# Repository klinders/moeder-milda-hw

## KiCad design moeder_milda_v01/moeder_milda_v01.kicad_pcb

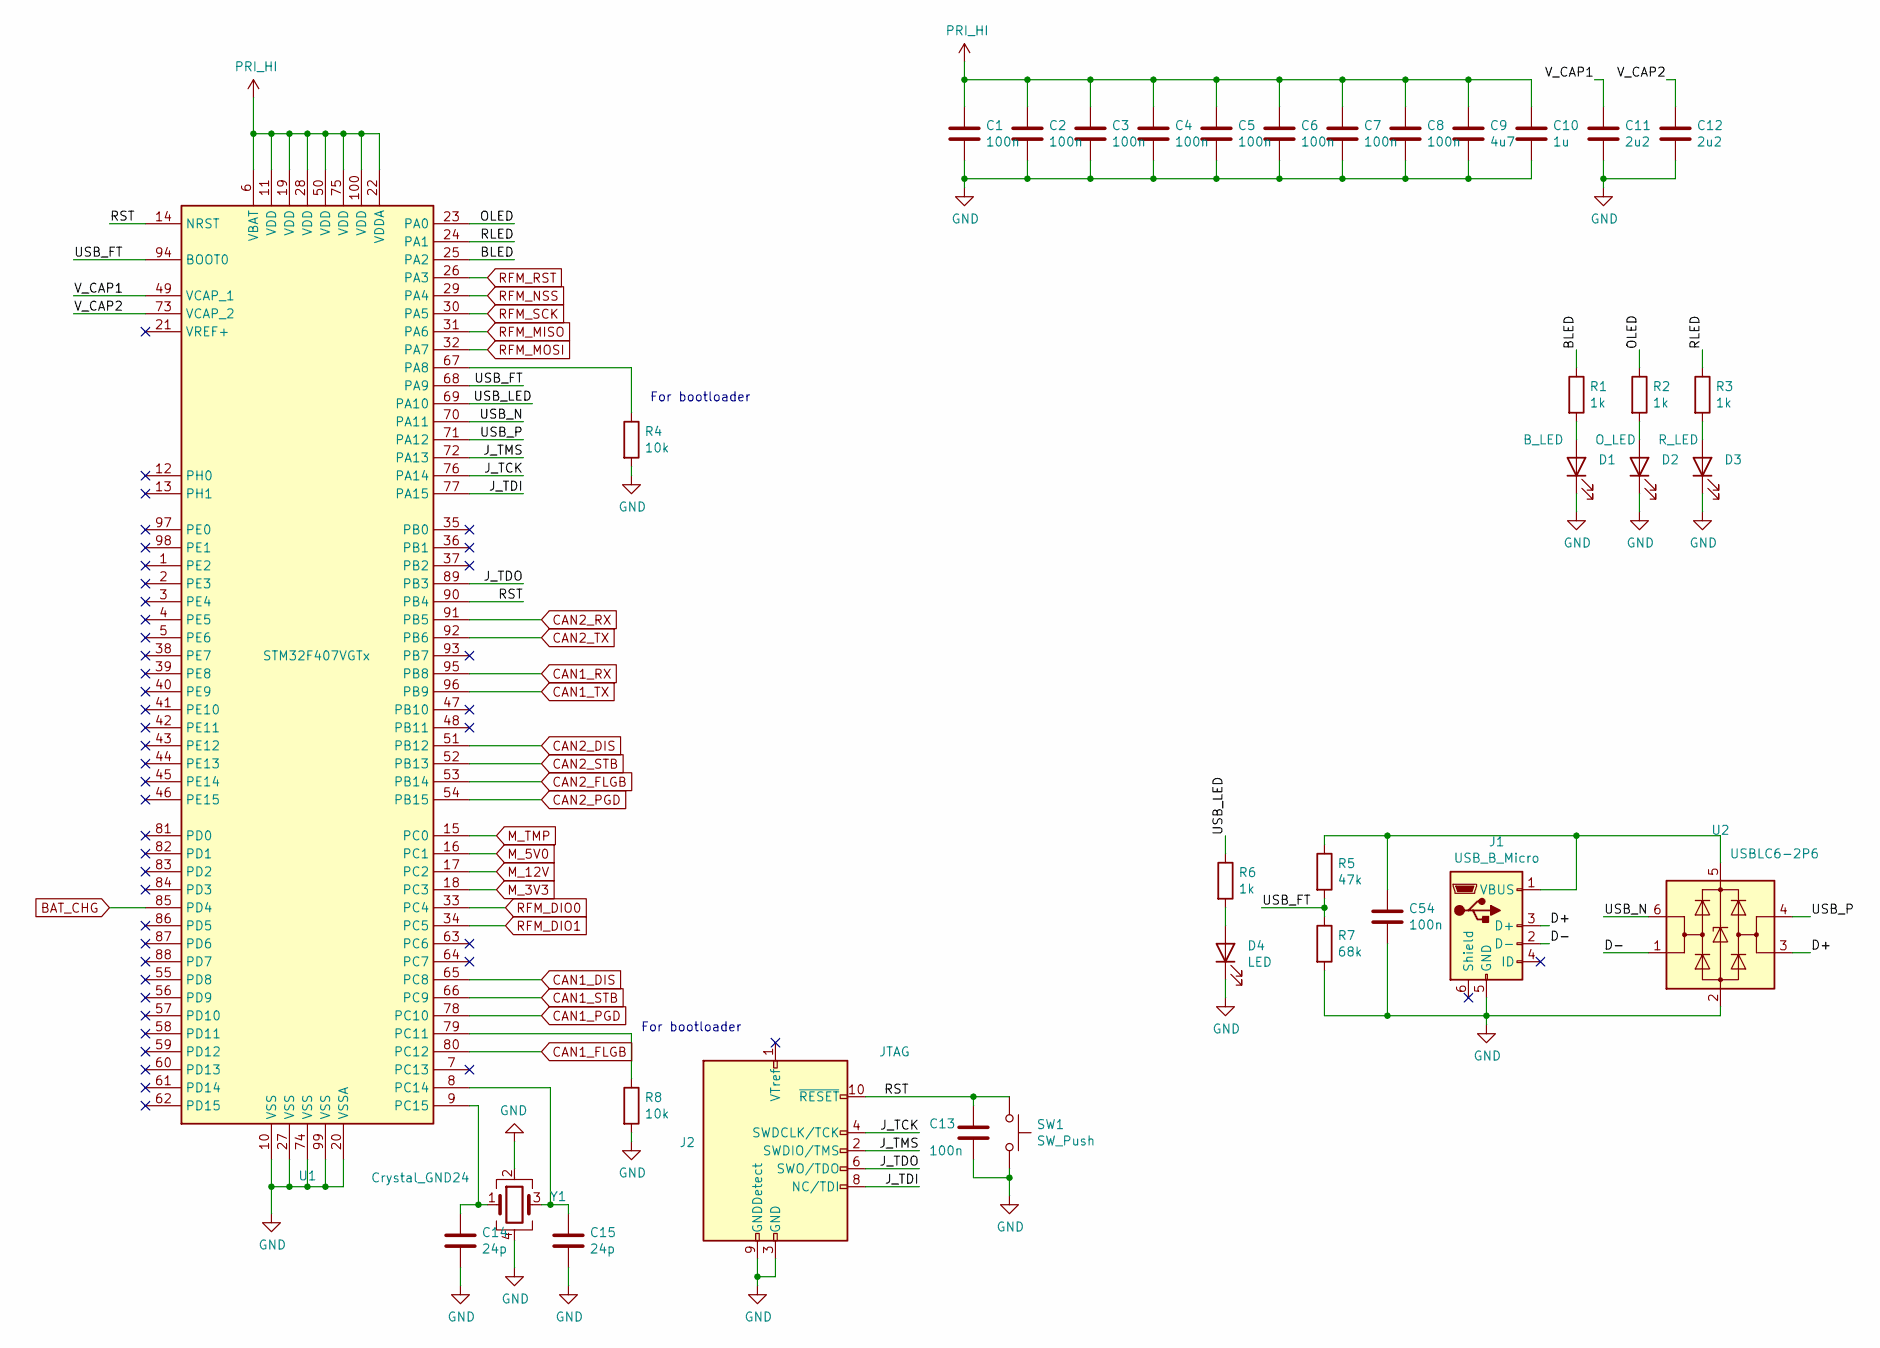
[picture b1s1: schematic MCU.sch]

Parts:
C1, C2, C3, C4, C5, C6, C7, C8, C13, C54: 100n; C_0603_1608Metric_Pad1.05x0.95mm_HandSolder; DigiKey 399-1099-1-ND
C9: 4u7; C_0805_2012Metric_Pad1.15x1.40mm_HandSolder; DigiKey 490-14466-1-ND
C10: 1u; C_0603_1608Metric_Pad1.05x0.95mm_HandSolder; DigiKey 1276-6524-1-ND
C11, C12: 2u2; C_0603_1608Metric_Pad1.05x0.95mm_HandSolder; DigiKey 587-4864-1-ND
C14, C15: 24p; C_0603_1608Metric_Pad1.05x0.95mm_HandSolder; DigiKey 490-1336-1-ND
D1: B_LED; LED_0603_1608Metric_Pad1.05x0.95mm_HandSolder; DigiKey 475-2815-1-ND
D2: O_LED; LED_0603_1608Metric_Pad1.05x0.95mm_HandSolder; DigiKey 475-2486-2-ND
D3: R_LED; LED_0603_1608Metric_Pad1.05x0.95mm_HandSolder; DigiKey 475-2512-1-ND
D4: LED; LED_0603_1608Metric_Pad1.05x0.95mm_HandSolder; DigiKey 475-2815-1-ND
J1: USB_B_Micro; USB_Micro-B_Molex_47346-0001; DigiKey WM17141CT-ND
J2: JTAG; PinHeader_2x05_P1.27mm_Vertical; DigiKey 1175-1627-ND
R1, R2, R3, R6: 1k; R_0603_1608Metric_Pad1.05x0.95mm_HandSolder
R4, R8: 10k; R_0603_1608Metric_Pad1.05x0.95mm_HandSolder
R5: 47k; R_0603_1608Metric_Pad1.05x0.95mm_HandSolder
R7: 68k; R_0603_1608Metric_Pad1.05x0.95mm_HandSolder
SW1: SW_Push; SW_SPST_B3S-1000; DigiKey SW836CT-ND
U1: STM32F407VGTx; LQFP-100_14x14mm_P0.5mm; DigiKey 497-11605-ND
U2: USBLC6-2P6; SOT-666; DigiKey 497-5026-1-ND
Y1: Crystal_GND24; Crystal_SMD_Abracon_ABM3B-4Pin_5.0x3.2mm; DigiKey 535-9720-1-ND

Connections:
/MCU/BLED: R1.1, U1.25 (PA2)
/MCU/D+: J1.3 (D+), U2.3 (I/O2)
/MCU/D-: J1.2 (D-), U2.1 (I/O1)
/MCU/J_TCK: J2.4 (SWDCLK/TCK), U1.76 (PA14)
/MCU/J_TDI: J2.8 (NC/TDI), U1.77 (PA15)
/MCU/J_TDO: J2.6 (SWO/TDO), U1.89 (PB3)
/MCU/J_TMS: J2.2 (SWDIO/TMS), U1.72 (PA13)
/MCU/OLED: R2.1, U1.23 (PA0)
/MCU/RLED: R3.1, U1.24 (PA1)
/MCU/RST: C13.1, J2.10 (~RESET~), SW1.1, U1.14 (NRST), U1.90 (PB4)
/MCU/USB_FT: R5.2, R7.1, U1.68 (PA9), U1.94 (BOOT0)
/MCU/USB_LED: R6.1, U1.69 (PA10)
/MCU/USB_N: U1.70 (PA11), U2.6 (I/O1)
/MCU/USB_P: U1.71 (PA12), U2.4 (I/O2)
/MCU/V_CAP1: C11.1, U1.49 (VCAP_1)
/MCU/V_CAP2: C12.1, U1.73 (VCAP_2)
BAT_CHG: U1.85 (PD4); also elsewhere on the board
CAN1_DIS: U1.65 (PC8); also elsewhere on the board
CAN1_FLGB: U1.80 (PC12); also elsewhere on the board
CAN1_PGD: U1.78 (PC10); also elsewhere on the board
CAN1_RX: U1.95 (PB8); also elsewhere on the board
CAN1_STB: U1.66 (PC9); also elsewhere on the board
CAN1_TX: U1.96 (PB9); also elsewhere on the board
CAN2_DIS: U1.51 (PB12); also elsewhere on the board
CAN2_FLGB: U1.53 (PB14); also elsewhere on the board
CAN2_PGD: U1.54 (PB15); also elsewhere on the board
CAN2_RX: U1.91 (PB5); also elsewhere on the board
CAN2_STB: U1.52 (PB13); also elsewhere on the board
CAN2_TX: U1.92 (PB6); also elsewhere on the board
GND: C1.2, C2.2, C3.2, C4.2, C5.2, C6.2, C7.2, C8.2, C9.2, C10.2, C11.2, C12.2, C13.2, C14.2, C15.2, C54.2, D1.1 (K), D2.1 (K), D3.1 (K), D4.1 (K), J1.5 (GND), J2.3 (GND), J2.5 (GND), J2.9 (GNDDetect), R4.2, R7.2, R8.2, SW1.2, U1.10 (VSS), U1.20 (VSSA), U1.27 (VSS), U1.74 (VSS), U1.99 (VSS), U2.2 (GND), Y1.2, Y1.4; also elsewhere on the board
M_3V3: U1.18 (PC3); also elsewhere on the board
M_5V0: U1.16 (PC1); also elsewhere on the board
M_12V: U1.17 (PC2); also elsewhere on the board
M_TMP: U1.15 (PC0); also elsewhere on the board
unnamed: C14.1, U1.9 (PC15), Y1.1
unnamed: C15.1, U1.8 (PC14), Y1.3
unnamed: C54.1, J1.1 (VBUS), R5.1, U2.5 (VBUS)
unnamed: D1.2 (A), R1.2
unnamed: D2.2 (A), R2.2
unnamed: D3.2 (A), R3.2
unnamed: D4.2 (A), R6.2
unnamed: R4.1, U1.67 (PA8)
unnamed: R8.1, U1.79 (PC11)
PRI_HI: C1.1, C2.1, C3.1, C4.1, C5.1, C6.1, C7.1, C8.1, C9.1, C10.1, U1.6 (VBAT), U1.11 (VDD), U1.19 (VDD), U1.22 (VDDA), U1.28 (VDD), U1.50 (VDD), U1.75 (VDD), U1.100 (VDD); also elsewhere on the board
RFM_DIO0: U1.33 (PC4); also elsewhere on the board
RFM_DIO1: U1.34 (PC5); also elsewhere on the board
RFM_MISO: U1.31 (PA6); also elsewhere on the board
RFM_MOSI: U1.32 (PA7); also elsewhere on the board
RFM_NSS: U1.29 (PA4); also elsewhere on the board
RFM_RST: U1.26 (PA3); also elsewhere on the board
RFM_SCK: U1.30 (PA5); also elsewhere on the board

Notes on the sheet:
For bootloader

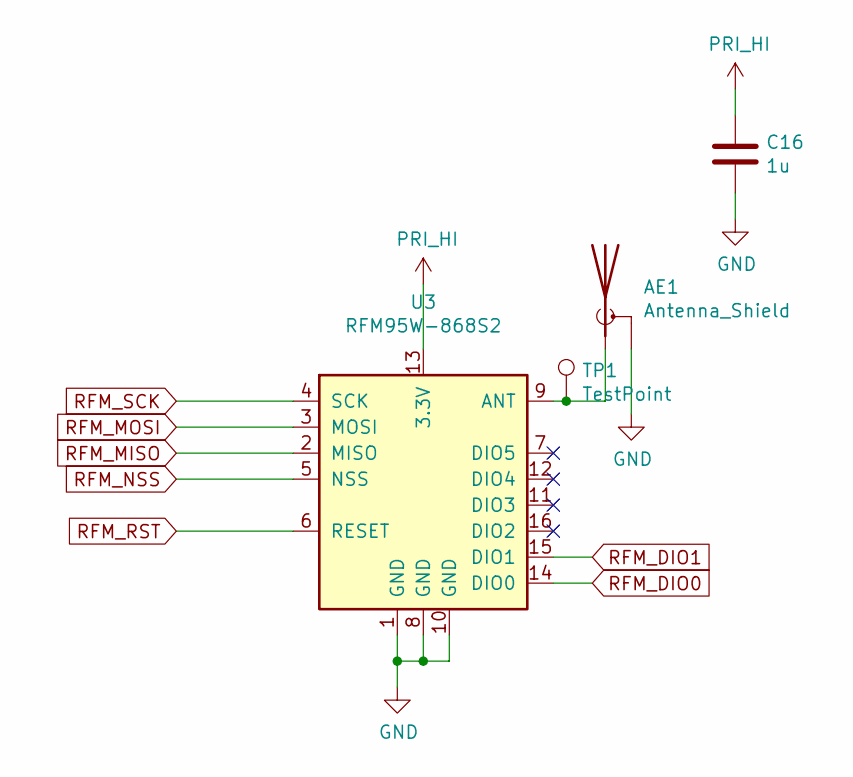
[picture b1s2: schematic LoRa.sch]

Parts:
AE1: Antenna_Shield; SMA_Molex_73251-1153_EdgeMount_Horizontal; DigiKey WM5534-ND
C16: 1u; C_0603_1608Metric_Pad1.05x0.95mm_HandSolder; DigiKey 1276-6524-1-ND
TP1: TestPoint; Curved_RF
U3: RFM95W-868S2; HOPERF_RFM9XW_SMD; DigiKey RFM95W-868S2-ND

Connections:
GND: AE1.2 (Shield), C16.2, U3.1 (GND), U3.8 (GND), U3.10 (GND); also elsewhere on the board
unnamed: AE1.1 (A), TP1.1, U3.9 (ANT)
PRI_HI: C16.1, U3.13 (3.3V); also elsewhere on the board
RFM_DIO0: U3.14 (DIO0); also elsewhere on the board
RFM_DIO1: U3.15 (DIO1); also elsewhere on the board
RFM_MISO: U3.2 (MISO); also elsewhere on the board
RFM_MOSI: U3.3 (MOSI); also elsewhere on the board
RFM_NSS: U3.5 (NSS); also elsewhere on the board
RFM_RST: U3.6 (RESET); also elsewhere on the board
RFM_SCK: U3.4 (SCK); also elsewhere on the board

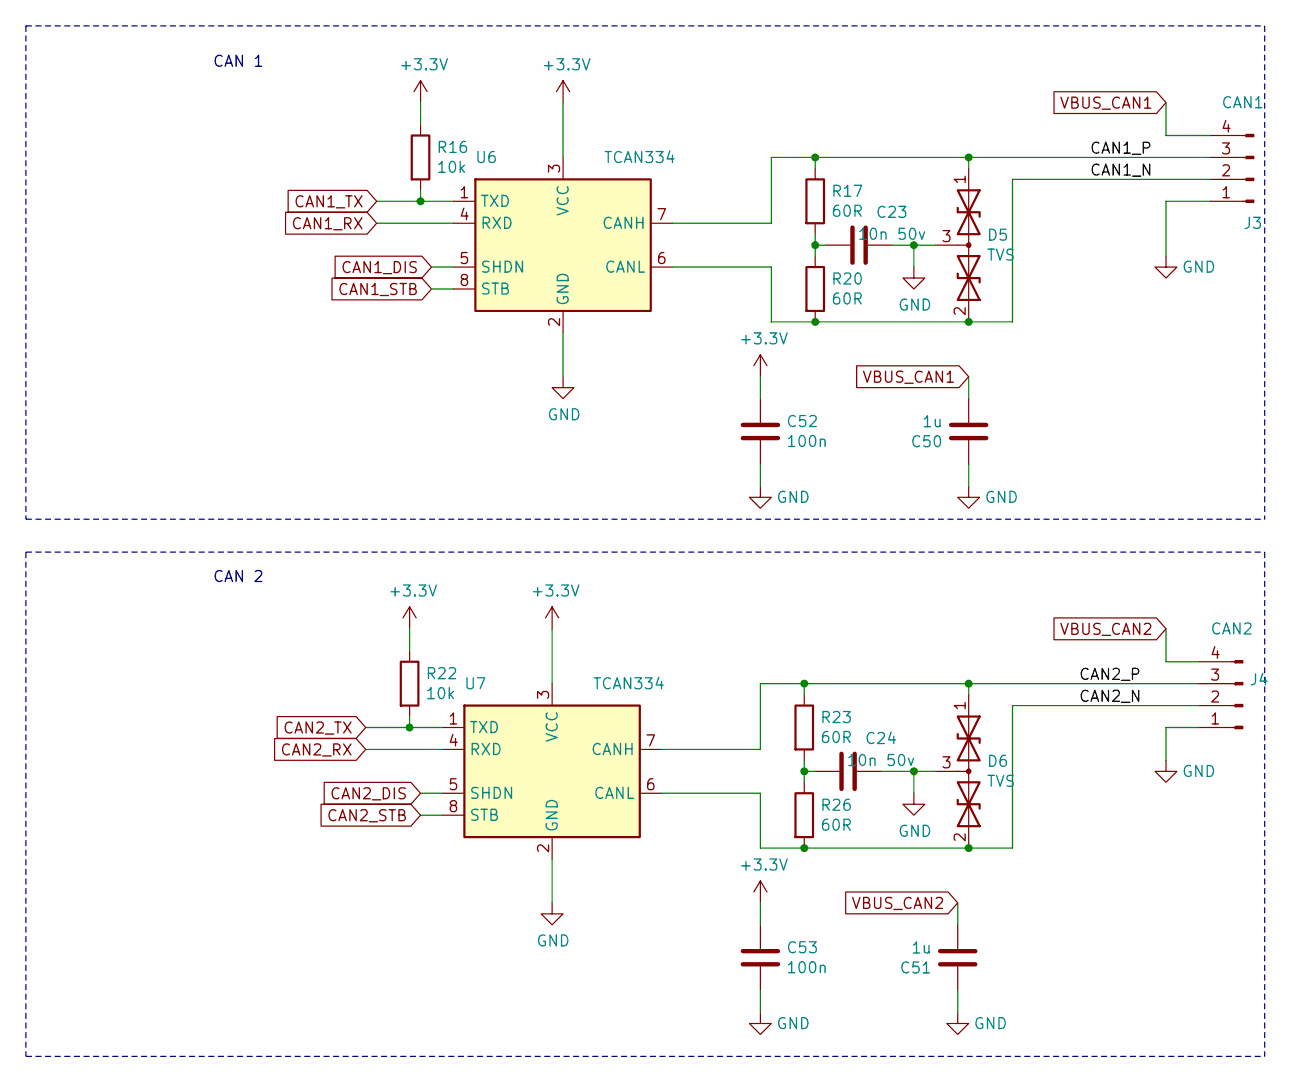
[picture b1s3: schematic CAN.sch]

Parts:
C23, C24: 10n 50v; C_0603_1608Metric_Pad1.05x0.95mm_HandSolder; DigiKey 399-17880-1-ND
C50, C51: 1u; C_0603_1608Metric_Pad1.05x0.95mm_HandSolder; DigiKey 1276-6524-1-ND
C52, C53: 100n; C_0603_1608Metric_Pad1.05x0.95mm_HandSolder; DigiKey 399-1099-1-ND
D5, D6: TVS; SOT-23_Handsoldering; DigiKey 296-24657-1-ND
J3: CAN1; PhoenixContact_MCV_1,5_4-G-5.08_1x04_P5.08mm_Vertical
J4: CAN2; PhoenixContact_MCV_1,5_4-G-5.08_1x04_P5.08mm_Vertical
R16, R22: 10k; R_0603_1608Metric_Pad1.05x0.95mm_HandSolder
R17, R20, R23, R26: 60R; R_0603_1608Metric_Pad1.05x0.95mm_HandSolder
U6, U7: TCAN334; SOIC-8_3.9x4.9mm_P1.27mm; DigiKey 296-44139-1-ND

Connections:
+3V3: C52.1, C53.1, R16.1, R22.1, U6.3 (VCC), U7.3 (VCC); also elsewhere on the board
/CAN/CAN1_N: D5.2 (A2), J3.2, R20.2, U6.6 (CANL)
/CAN/CAN1_P: D5.1 (A1), J3.3, R17.1, U6.7 (CANH)
/CAN/CAN2_N: D6.2 (A2), J4.2, R26.2, U7.6 (CANL)
/CAN/CAN2_P: D6.1 (A1), J4.3, R23.1, U7.7 (CANH)
CAN1_DIS: U6.5 (SHDN); also elsewhere on the board
CAN1_RX: U6.4 (RXD); also elsewhere on the board
CAN1_STB: U6.8 (STB); also elsewhere on the board
CAN1_TX: R16.2, U6.1 (TXD); also elsewhere on the board
CAN2_DIS: U7.5 (SHDN); also elsewhere on the board
CAN2_RX: U7.4 (RXD); also elsewhere on the board
CAN2_STB: U7.8 (STB); also elsewhere on the board
CAN2_TX: R22.2, U7.1 (TXD); also elsewhere on the board
GND: C23.2, C24.2, C50.1, C51.1, C52.2, C53.2, D5.3 (common), D6.3 (common), J3.1, J4.1, U6.2 (GND), U7.2 (GND); also elsewhere on the board
unnamed: C23.1, R17.2, R20.1
unnamed: C24.1, R23.2, R26.1
VBUS_CAN1: C50.2, J3.4; also elsewhere on the board
VBUS_CAN2: C51.2, J4.4; also elsewhere on the board

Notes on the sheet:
CAN 2
CAN 1

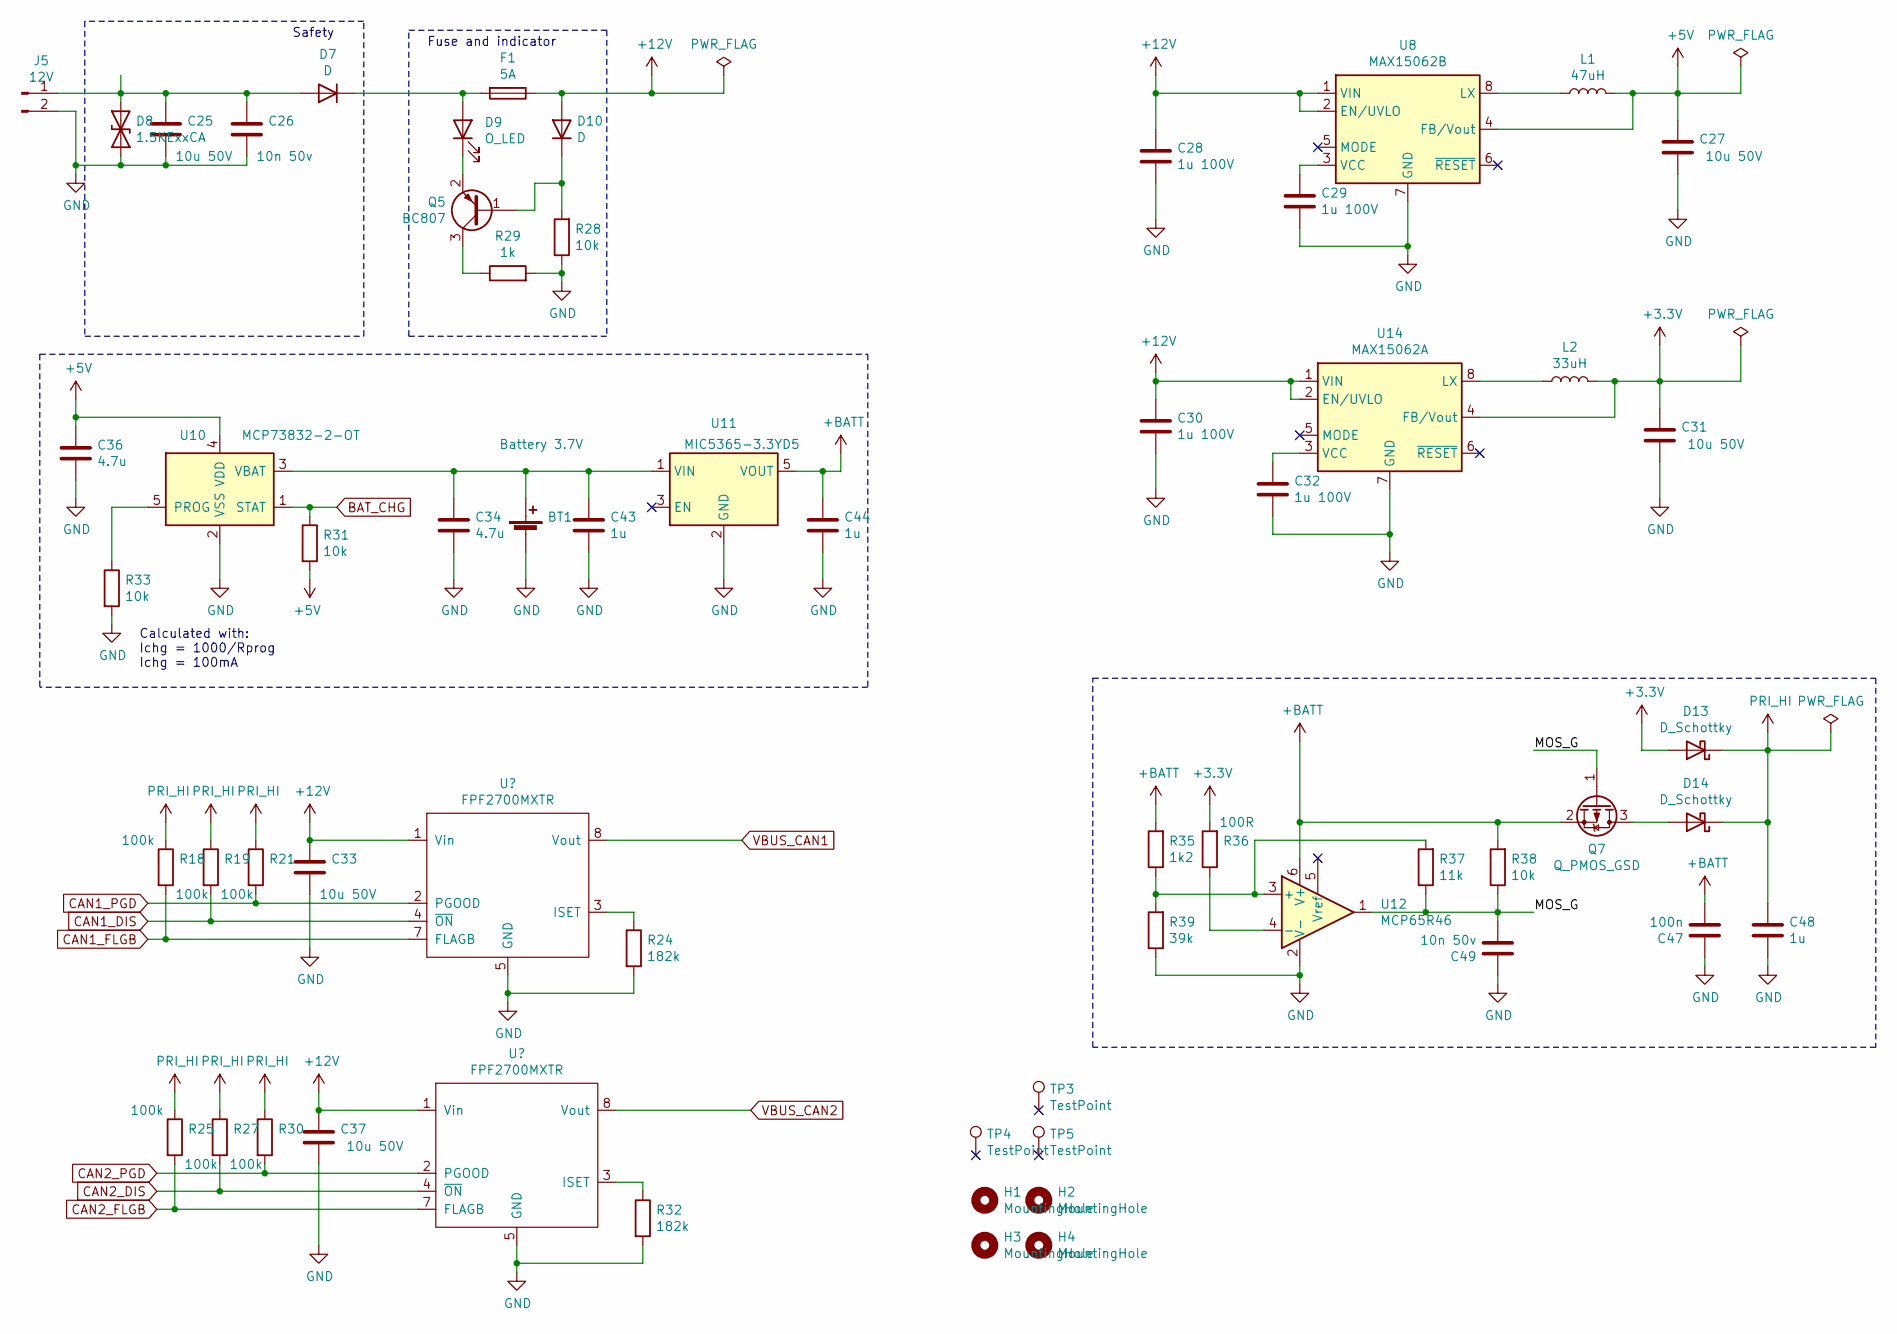
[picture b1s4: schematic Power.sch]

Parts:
BT1: Battery 3.7V; BatteryHolder_Keystone_1042_1x18650; DigiKey 36-1043-ND
C25, C27, C31, C33, C37: 10u 50V; C_1210_3225Metric_Pad1.42x2.65mm_HandSolder; DigiKey 399-11629-1-ND
C26, C49: 10n 50v; C_0603_1608Metric_Pad1.05x0.95mm_HandSolder; DigiKey 399-17880-1-ND
C28, C29, C30, C32: 1u 100V; C_1206_3216Metric_Pad1.42x1.75mm_HandSolder; DigiKey 311-1948-1-ND
C34, C36: 4.7u; C_0805_2012Metric_Pad1.15x1.40mm_HandSolder; DigiKey 490-14466-1-ND
C43, C44, C48: 1u; C_0603_1608Metric_Pad1.05x0.95mm_HandSolder; DigiKey 1276-6524-1-ND
C47: 100n; C_0603_1608Metric_Pad1.05x0.95mm_HandSolder; DigiKey 399-1099-1-ND
D7: D; D_SMC_Handsoldering; DigiKey SL54-TPMSCT-ND
D8: 1.5KExxCA; D_SMC_Handsoldering; DigiKey SMCJ17CALFCT-ND
D9: O_LED; LED_0603_1608Metric_Pad1.05x0.95mm_HandSolder; DigiKey 475-2486-2-ND
D10: D; D_SOD-323_HandSoldering; DigiKey ZHCS400CT-ND
D13, D14: D_Schottky; D_SOD-123; DigiKey 1727-3848-1-ND
F1: 5A; Fuse_1206_3216Metric_Castellated; DigiKey SF-1206F500-2CT-ND
H1, H2, H3, H4: MountingHole; MountingHole_3.2mm_M3_Pad_Via
J5: 12V; PhoenixContact_MCV_1,5_2-G-5.08_1x02_P5.08mm_Vertical
L1: 47uH; L_Bourns-SRN4018; DigiKey SRN4018TA-470MCT-ND
L2: 33uH; L_Bourns-SRN4018; DigiKey SRN4018-330MCT-ND
Q5: BC807; SOT-23_Handsoldering; DigiKey 1727-1875-1-ND
Q7: Q_PMOS_GSD; SOT-23_Handsoldering; DigiKey NTR3A30PZT1GOSCT-ND
R18, R19, R21, R25, R27, R30: 100k; R_0603_1608Metric_Pad1.05x0.95mm_HandSolder
R24, R32: 182k; R_0603_1608Metric_Pad1.05x0.95mm_HandSolder
R28, R31, R33, R38: 10k; R_0603_1608Metric_Pad1.05x0.95mm_HandSolder
R29: 1k; R_0603_1608Metric_Pad1.05x0.95mm_HandSolder
R35: 1k2; R_0603_1608Metric_Pad1.05x0.95mm_HandSolder
R36: 100R; R_0603_1608Metric_Pad1.05x0.95mm_HandSolder
R37: 11k; R_0603_1608Metric_Pad1.05x0.95mm_HandSolder
R39: 39k; R_0603_1608Metric_Pad1.05x0.95mm_HandSolder
TP3: TestPoint; WEEE-Logo_4.2x6mm_SilkScreen
TP4: TestPoint; Milda_bat
TP5: TestPoint; Milda_neon_fsilk
U8: MAX15062B; DFN-8_2x2mm_P0.5mm; DigiKey MAX15062BATA+TCT-ND
U10: MCP73832-2-OT; SOT-23-5; DigiKey MCP73832T-2ACI/OTCT-ND
U11: MIC5365-3.3YD5; SOT-23-5; DigiKey 576-4085-1-ND
U12: MCP65R46; SOT-23-6; DigiKey MCP65R41T-2402E/CHYCT-ND
U14: MAX15062A; DFN-8_2x2mm_P0.5mm; DigiKey MAX15062AATA+TCT-ND

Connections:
+3V3: C31.1, D13.2 (A), L2.2, R36.2, U14.4 (FB/Vout); also elsewhere on the board
+5V: C27.1, C36.1, L1.2, R31.2, U8.4 (FB/Vout), U10.4 (VDD); also elsewhere on the board
+12V: C28.1, C30.1, C33.1, C37.1, D10.2 (A), F1.1, U8.1 (VIN), U8.2 (EN/UVLO), U14.1 (VIN), U14.2 (EN/UVLO); also elsewhere on the board
+BATT: C44.1, C47.2, Q7.2 (S), R35.2, R38.2, U11.5 (VOUT), U12.6 (V+)
/Power/MOS_G: C49.2, Q7.1 (G), R37.1, R38.1, U12.1
BAT_CHG: R31.1, U10.1 (STAT); also elsewhere on the board
CAN1_DIS: R19.2; also elsewhere on the board
CAN1_FLGB: R18.2; also elsewhere on the board
CAN1_PGD: R21.2; also elsewhere on the board
CAN2_DIS: R27.2; also elsewhere on the board
CAN2_FLGB: R25.2; also elsewhere on the board
CAN2_PGD: R30.2; also elsewhere on the board
GND: BT1.2 (-), C25.2, C26.2, C27.2, C28.2, C29.2, C30.2, C31.2, C32.2, C33.2, C34.2, C36.2, C37.2, C43.2, C44.2, C47.1, C48.2, C49.1, D8.2 (A2), J5.2, R24.2, R28.1, R29.2, R32.2, R33.2, R39.1, U8.7 (GND), U10.2 (VSS), U11.2 (GND), U12.2 (V-), U14.7 (GND); also elsewhere on the board
unnamed: BT1.1 (+), C34.1, C43.1, U10.3 (VBAT), U11.1 (VIN)
unnamed: C25.1, C26.1, D7.2 (A), D8.1 (A1), J5.1
unnamed: C29.1, U8.3 (VCC)
unnamed: C32.1, U14.3 (VCC)
unnamed: D7.1 (K), D9.2 (A), F1.2
unnamed: D9.1 (K), Q5.2 (E)
unnamed: D10.1 (K), Q5.1 (B), R28.2
unnamed: D14.2 (A), Q7.3 (D)
unnamed: L1.1, U8.8 (LX)
unnamed: L2.1, U14.8 (LX)
unnamed: Q5.3 (C), R29.1
unnamed 71: R24.1; also elsewhere on the board
unnamed 72: R32.1; also elsewhere on the board
unnamed: R33.1, U10.5 (PROG)
unnamed: R35.1, R37.2, R39.2, U12.3 (+)
unnamed: R36.1, U12.4 (-)
PRI_HI: C48.1, D13.1 (K), D14.1 (K), R18.1, R19.1, R21.1, R25.1, R27.1, R30.1; also elsewhere on the board

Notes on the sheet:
Calculated with: Ichg = 1000/Rprog Ichg = 100mA
Fuse and indicator
Safety

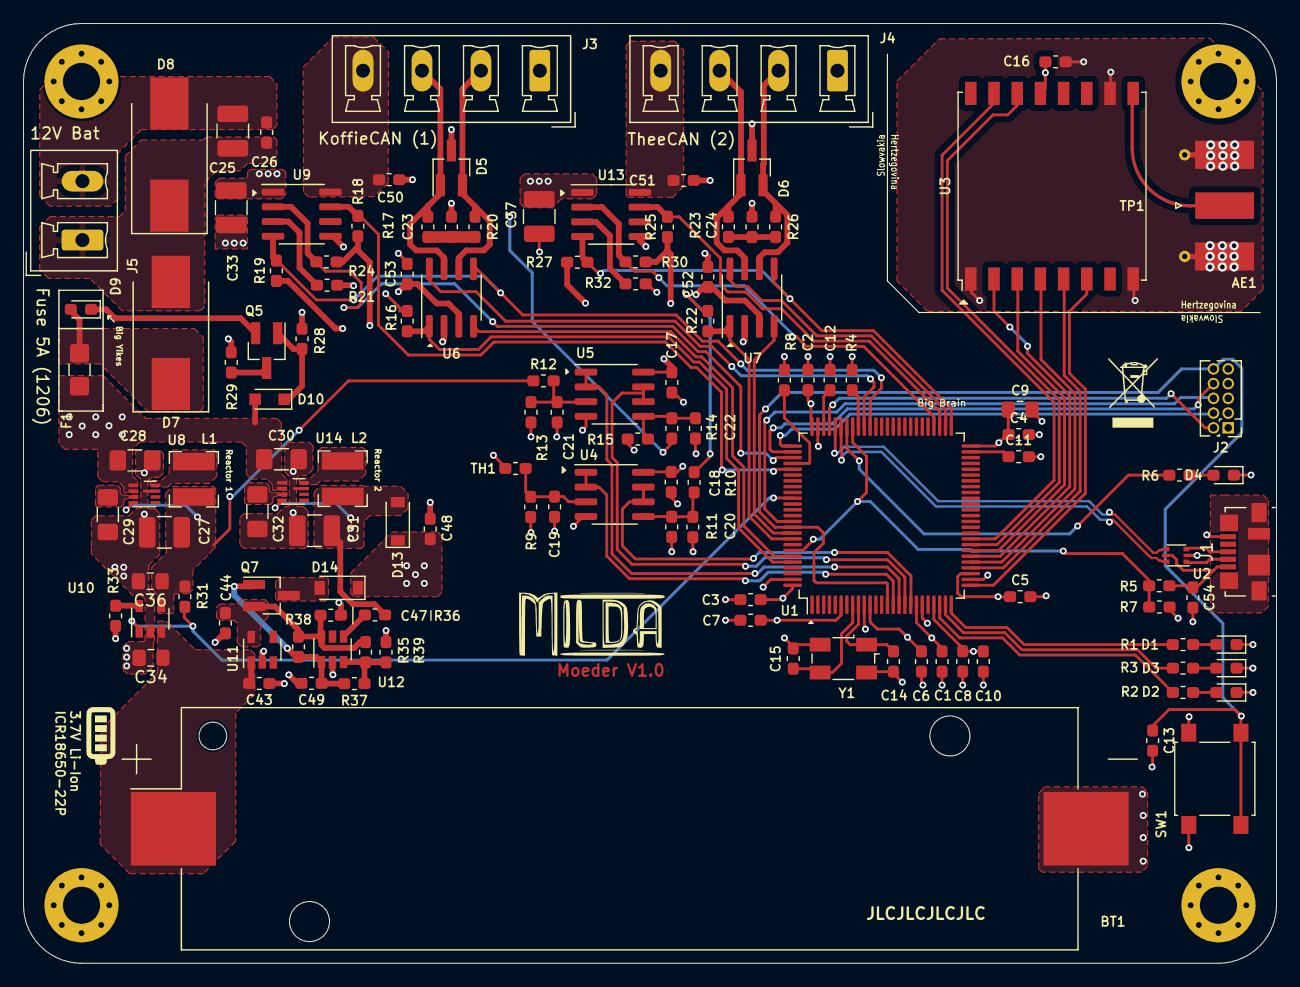
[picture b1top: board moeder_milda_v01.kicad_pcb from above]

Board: 4 copper layers, 108.0 x 81.0 mm, 133 parts (0 on the bottom side), 85 nets.

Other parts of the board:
C17, C18, C19, C20, C21, C22: 100n; C_0603_1608Metric_Pad1.05x0.95mm_HandSolder
R9: R; R_0603_1608Metric_Pad1.05x0.95mm_HandSolder
R10: 1k; R_0603_1608Metric_Pad1.05x0.95mm_HandSolder
R11, R14: 10k; R_0603_1608Metric_Pad1.05x0.95mm_HandSolder
R12: 2k2; R_0603_1608Metric_Pad1.05x0.95mm_HandSolder
R13, R15: 3k3; R_0603_1608Metric_Pad1.05x0.95mm_HandSolder
TH1: NTC 10k; R_0603_1608Metric_Pad1.05x0.95mm_HandSolder
U4, U5: LM2904; SOIC-8_3.9x4.9mm_P1.27mm
U9, U13: FPF2700MXTR; SOIC-8_3.9x4.9mm_P1.27mm

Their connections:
+3V3: R10.1; also elsewhere on the board
+5V: R12.1; also elsewhere on the board
+12V: R14.1, U9.1, U13.1; also elsewhere on the board
CAN1_DIS: U9.4; also elsewhere on the board
CAN1_FLGB: U9.7; also elsewhere on the board
CAN1_PGD: U9.2; also elsewhere on the board
CAN2_DIS: U13.4; also elsewhere on the board
CAN2_FLGB: U13.7; also elsewhere on the board
CAN2_PGD: U13.2; also elsewhere on the board
GND: C17.2, C18.2, C19.2, C20.2, C21.2, C22.2, R9.2, R11.2, R13.2, R15.2, U4.4, U5.4, U9.5, U13.5; also elsewhere on the board
M_3V3: U4.6, U4.7; also elsewhere on the board
M_5V0: U5.1, U5.2; also elsewhere on the board
M_12V: U5.6, U5.7; also elsewhere on the board
M_TMP: U4.1, U4.2; also elsewhere on the board
unnamed: C19.1, R9.1, TH1.2, U4.3
unnamed: C20.1, R10.2, R11.1, U4.5
unnamed: C21.1, R12.2, R13.1, U5.3
unnamed: C22.1, R14.2, R15.1, U5.5
unnamed 71: U9.3; also elsewhere on the board
unnamed 72: U13.3; also elsewhere on the board
PRI_HI: C17.1, C18.1, TH1.1, U4.8, U5.8; also elsewhere on the board
VBUS_CAN1: U9.8; also elsewhere on the board
VBUS_CAN2: U13.8; also elsewhere on the board

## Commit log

2020-06-01 Added .gitignore
2020-06-01 added 3D image to output
